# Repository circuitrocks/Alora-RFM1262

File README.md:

# Alora-RFM1262 support files for the Alora RFM1262 boards.    
This repository contains the HW and SW support files for the [Circuitrocks Alora RFM1262](https://circuit.rocks/lora) board. 

The board is compatible with the [Adafruit Feather specifications](https://learn.adafruit.com/adafruit-feather?view=all). But it is tested only with the [Adafruit Feather HUZZAH ESP8266](https://circuit.rocks/wifi-feather-huzzah-esp8266-adafruit.html) and the [Adafruit HUZZAH32 ESP32](https://circuit.rocks/huzzah32-esp32-feather-board-adafruit.html) Feathers.

## Hardware
[Eagle format schematic and PCB files](https://github.com/circuitrocks/Alora-RFM1262/tree/master/Hardware/Eagle)    
[Schematic as PDF file](https://github.com/circuitrocks/Alora-RFM1262/tree/master/Hardware)    
[3D files of the board in Autodesk Fusion 360 and STEP format](https://github.com/circuitrocks/Alora-RFM1262/tree/master/Hardware/3D)    

## Software
At the moment there are two Arduino libraries available that support the Semtech SX1262 chips.
- [RadioLib](https://github.com/jgromes/RadioLib) by Jan Gromes
- [SX126x-Arduino](https://github.com/beegee-tokyo/SX126x-Arduino) by Bernd Giesecke

Please check the ArduinoIDE or PlatformIO documentation how to install the libraries.

The first one is easier to use and supports most Arduino HW platforms.
The second one is more complicated and supports only ESP8266, ESP32 and nRF52 HW platforms. **_But it supports LoRaWan_** and it has a working example for a **_single channel LoRaWan gateway_**.

It is recommended to use the RadioLib library if you just want to do simple LoRa communication. But if you want to connect your Alora SX1262 module to LoRaWan you should choose the SX126x-Arduino library.

Examples for both libraries can be found in the folders [Using_SX1262x_Arduino](https://github.com/circuitrocks/Alora-RFM1262/tree/master/Software/Using_SX126x_Arduino) and [Using_RadioLib](https://github.com/circuitrocks/Alora-RFM1262/tree/master/Software/Using_RadioLib).    
Most examples are available for ArduinoIDE and PlatformIO. But if you are serious in programming, I strongly recommend you switch to PlatformIO as your development IDE.

- RadioLib examples
  - [RFM1262-PING](https://github.com/circuitrocks/Alora-RFM1262/tree/master/Software/Using_RadioLib/ArduinoIDE/RFM1262-PING) and [RFM1262-PONG](https://github.com/circuitrocks/Alora-RFM1262/tree/master/Software/Using_RadioLib/ArduinoIDE/RFM1262-PONG) are simple communication examples between two LoRa nodes using the RadioLib library. These examples are for ArduinoIDE.
  - [RFM1262-PING](https://github.com/circuitrocks/Alora-RFM1262/tree/master/Software/Using_RadioLib/PlatformIO/RFM1262-PING) and [RFM1262-PONG](https://github.com/circuitrocks/Alora-RFM1262/tree/master/Software/Using_RadioLib/PlatformIO/RFM1262-PONG) are simple communication examples between two LoRa nodes using the RadioLib library. These examples are for PlatformIO.
- SX126x-Arduino examples
  - [PingPong](https://github.com/circuitrocks/Alora-RFM1262/tree/master/Software/Using_SX126x_Arduino/ArduinoIDE/PingPong) is a simple communication example between two LoRa nodes using the SX126x_Arduino library with ArduinoIDE
  - [LoRaWanPio](https://github.com/circuitrocks/Alora-RFM1262/tree/master/Software/Using_SX126x_Arduino/PlatformIO/LoRaWanPio) is an example for a LoRaWan node.
  - [SX1262-SC-GW](https://github.com/circuitrocks/Alora-RFM1262/tree/master/Software/Using_SX126x_Arduino/PlatformIO/SX1262-SC-GW) is a single channel LoRaWan gateway. The code is based on the [ESP-1ch-Gateway-v6.0](https://github.com/things4u/ESP-1ch-Gateway-v6.0) single channel LoRaWan gateway. It was ported from from Semtech SX127x to Semttech SX1262 LoRa chips. More information can be found in the [readme](https://github.com/circuitrocks/Alora-RFM1262/blob/master/Software/Using_SX126x_Arduino/PlatformIO/SX1262-SC-GW/README.md) for this application.

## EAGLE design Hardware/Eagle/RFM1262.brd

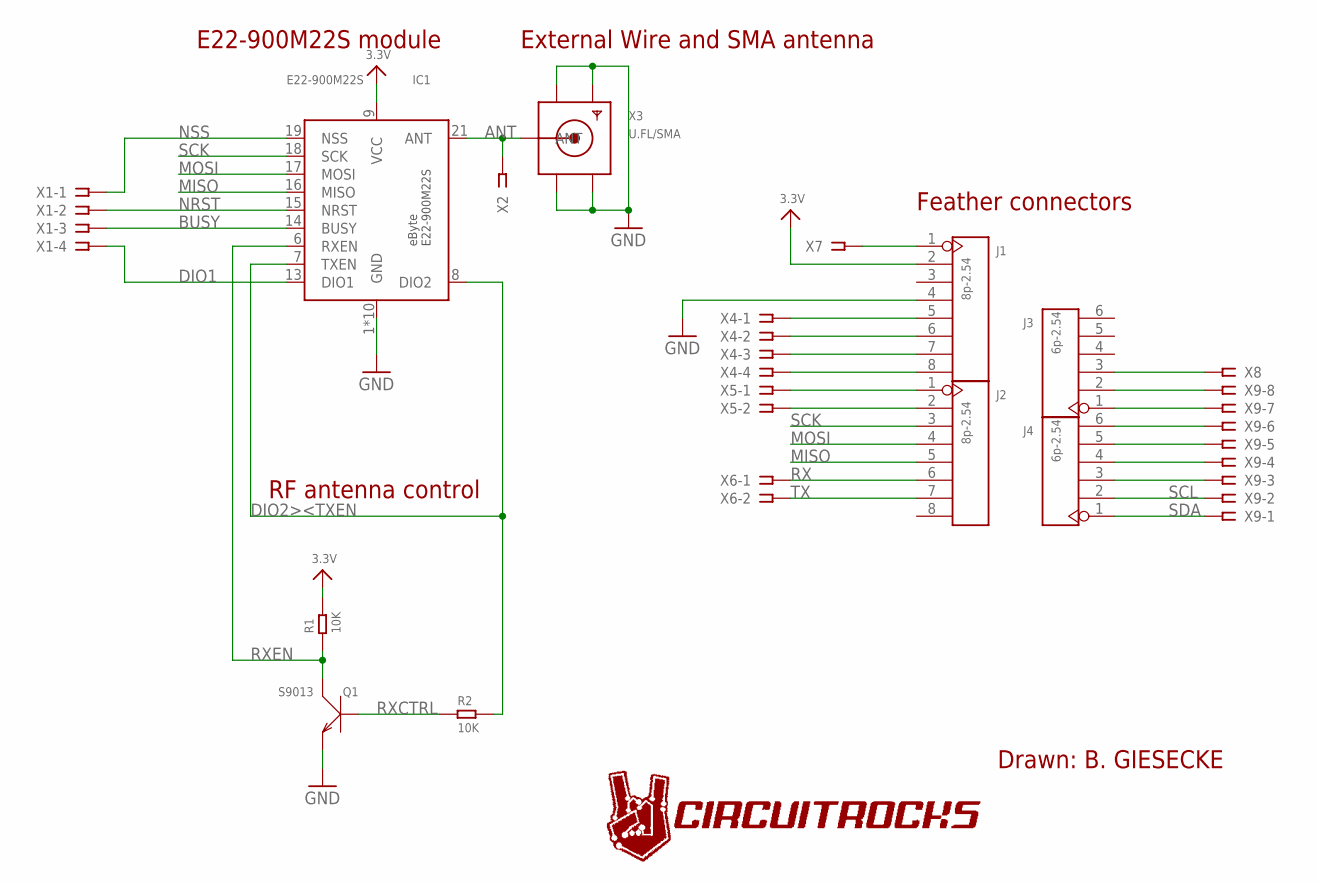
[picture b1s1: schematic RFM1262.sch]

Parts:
IC1: E22-900M22S
J1, J2: 8p-2.54; H8-2.54
J3, J4: 6p-2.54; H6-2.54
Q1: S9013; SOT-23
R1, R2: 10K; R0805
X1, X4: SSW-104-02-G-S
X2, X7, X8: SSW-101-02-G-S
X3: U.FL/SMA; SMA_EDGELAUNCH_UFL
X5, X6: SSW-102-02-G-S
X9: SSW-108-02-G-S

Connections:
3.3V: IC1.9 (VCC), J1.2, R1.2
ANT: IC1.21 (ANT), X2.1, X3.P (ANT)
BUSY: IC1.14 (BUSY), X1.3
DIO1: IC1.13 (DIO1), X1.4
DIO2><TXEN: IC1.7 (TXEN), IC1.8 (DIO2), R2.2
GND: IC1.1 (GND), IC1.2 (GND), IC1.3 (GND), IC1.4 (GND), IC1.5 (GND), IC1.10 (GND), IC1.11 (GND), IC1.12 (GND), IC1.20 (GND), IC1.22 (GND), J1.4, Q1.2 (E), X3.GND@1 (GND1), X3.GND@2 (GND2), X3.GND@3 (GND3), X3.GND@4 (GND4)
MISO: IC1.16 (MISO), J2.5
MOSI: IC1.17 (MOSI), J2.4
unnamed: J1.1, X7.1
unnamed: J3.3, X8.1
unnamed: J1.5, X4.1
unnamed: J1.6, X4.2
unnamed: J1.7, X4.3
unnamed: J1.8, X4.4
unnamed: J2.1, X5.1
unnamed: J2.2, X5.2
unnamed: J3.2, X9.8
unnamed: J3.1, X9.7
unnamed: J4.6, X9.6
unnamed: J4.5, X9.5
unnamed: J4.4, X9.4
unnamed: J4.3, X9.3
NRST: IC1.15 (NRST), X1.2
NSS: IC1.19 (NSS), X1.1
RX: J2.6, X6.1
RXCTRL: Q1.1 (B), R2.1
RXEN: IC1.6 (RXEN), Q1.3 (C), R1.1
SCK: IC1.18 (SCK), J2.3
SCL: J4.2, X9.2
SDA: J4.1, X9.1
TX: J2.7, X6.2

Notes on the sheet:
Drawn: B. GIESECKE
E22-900M22S module
External Wire and SMA antenna
Feather connectors
RF antenna control

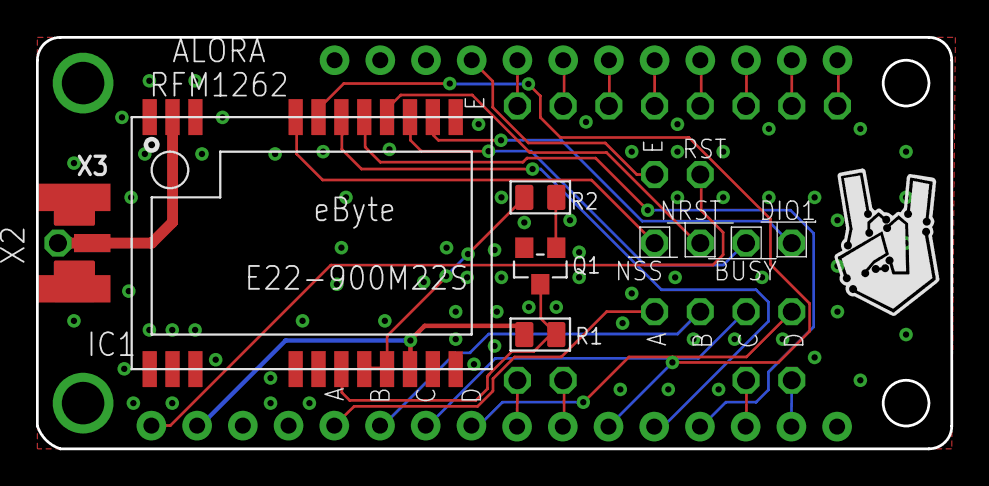
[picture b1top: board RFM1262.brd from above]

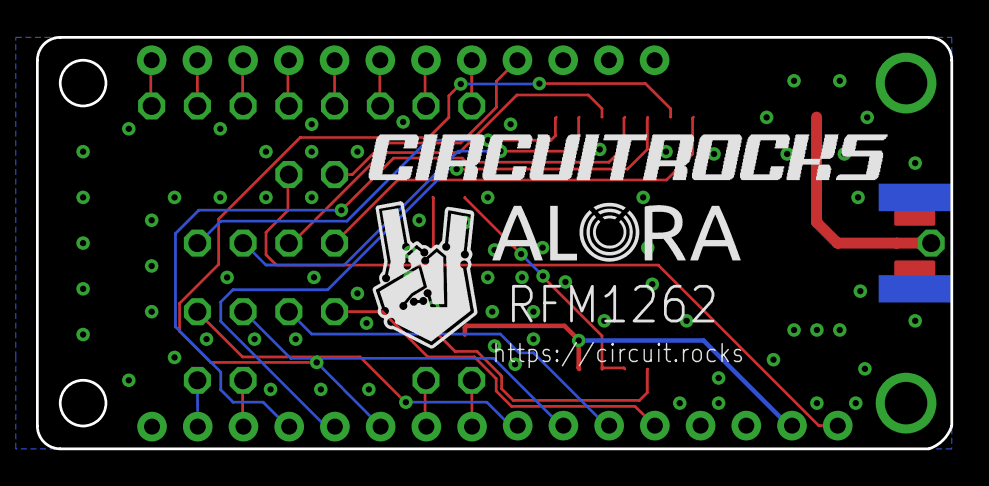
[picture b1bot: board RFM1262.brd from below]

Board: 2 copper layers, 50.8 x 22.9 mm, 17 parts (4 on the bottom side), 31 nets.

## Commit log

2019-11-27 Adding content
2019-12-10 Add product sheet.
2019-12-21 Update examples
